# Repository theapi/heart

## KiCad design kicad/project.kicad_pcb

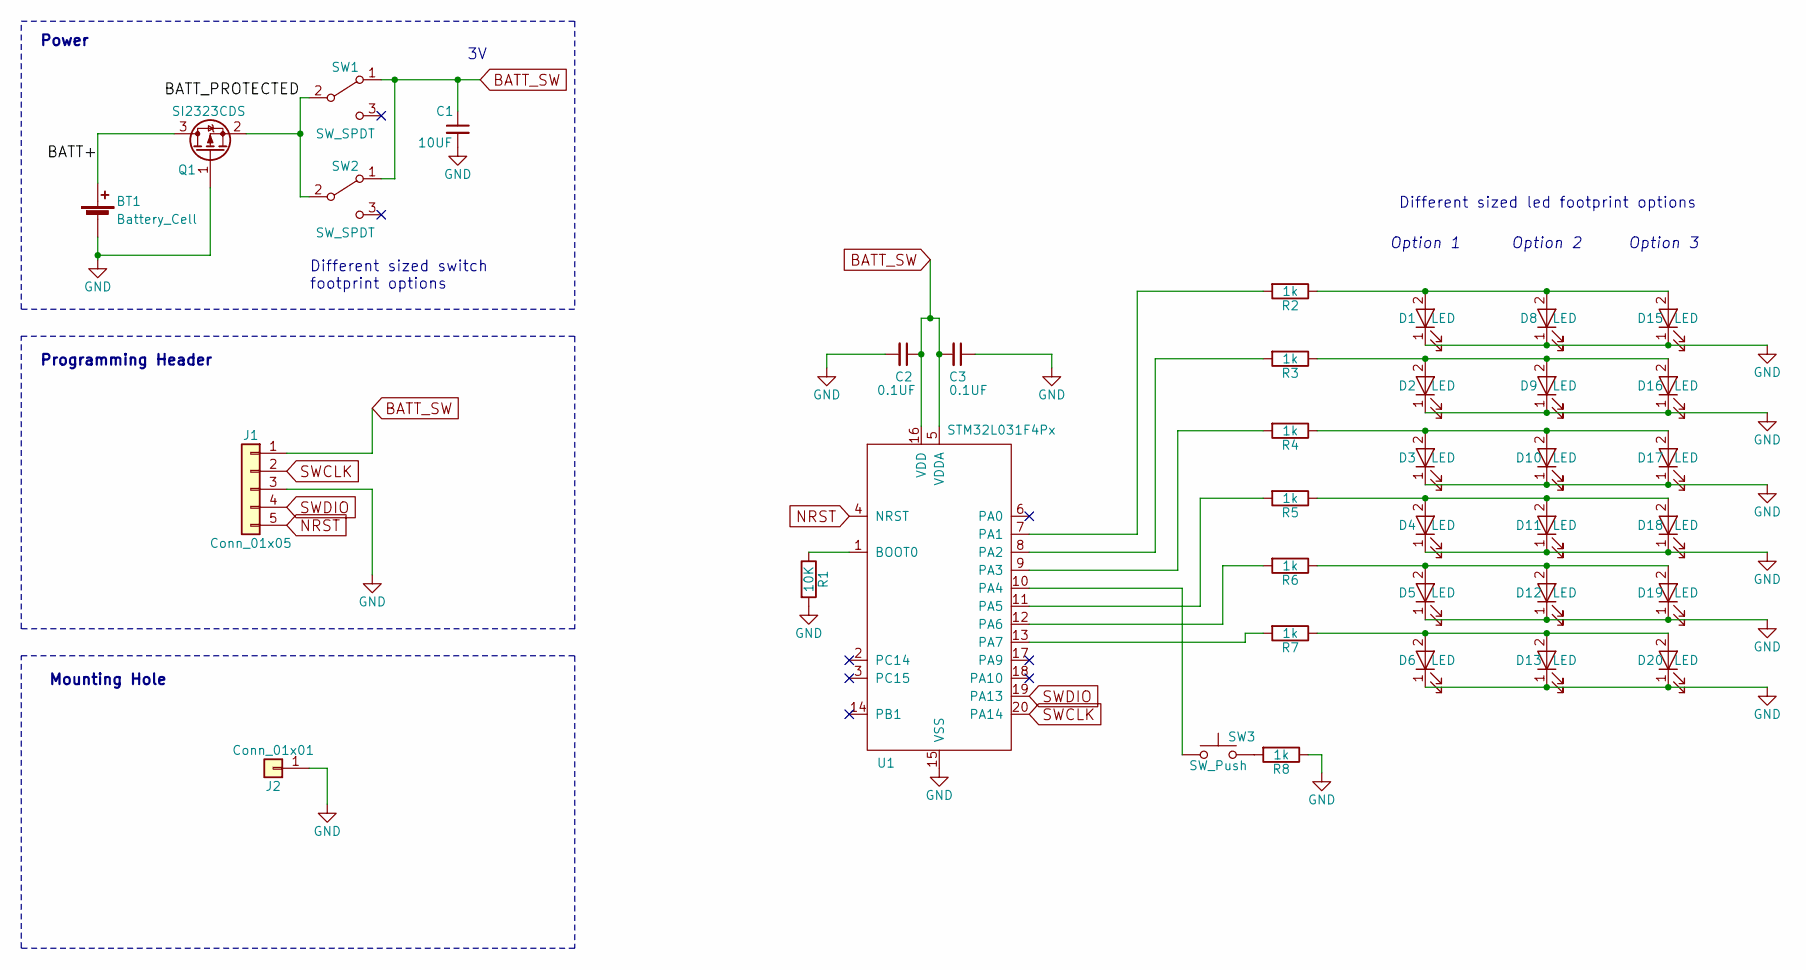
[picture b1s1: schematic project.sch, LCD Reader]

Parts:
BT1: Battery_Cell; CR2032H
C1: 10UF; C_0805_HandSoldering
C2, C3: 0.1UF; C_0805_HandSoldering
D1, D2, D3, D4, D5, D6: LED; LED_0805
D8, D9, D10, D11, D12, D13: LED; LED_D5.0mm
D15, D16, D17, D18, D19, D20: LED; LED_1206
J1: Conn_01x05; SWD_Header
J2: Conn_01x01; MountingHole_2.2mm_M2_ISO7380_Pad
Q1: SI2323CDS; SOT-23_Handsoldering
R1: 10K; R_0603_HandSoldering
R2, R3, R4, R5, R6, R7, R8: 1k; R_0603_HandSoldering
SW1, SW2: SW_SPDT; SW_Micro_SPST
SW3: SW_Push; SW_PUSH_6mm
U1: STM32L031F4Px; TSSOP-20_4.4x6.5mm_Pitch0.65mm

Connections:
/BATT+: BT1.1 (+), Q1.3 (D)
/BATT_PROTECTED: Q1.2 (S), SW1.2 (B), SW2.2 (B)
BATT_SW: C1.1, C2.1, C3.2, J1.1, SW1.1 (A), SW2.1 (A), U1.5 (VDDA), U1.16 (VDD)
GND: BT1.2 (-), C1.2, C2.2, C3.1, D1.1 (K), D2.1 (K), D3.1 (K), D4.1 (K), D5.1 (K), D6.1 (K), D8.1 (K), D9.1 (K), D10.1 (K), D11.1 (K), D12.1 (K), D13.1 (K), D15.1 (K), D16.1 (K), D17.1 (K), D18.1 (K), D19.1 (K), D20.1 (K), J1.3, J2.1, Q1.1 (G), R1.2, R8.1, U1.15 (VSS)
NRST: J1.5, U1.4 (NRST)
unnamed: D1.2 (A), D8.2 (A), D15.2 (A), R2.1
unnamed: D3.2 (A), D10.2 (A), D17.2 (A), R4.1
unnamed: D4.2 (A), D11.2 (A), D18.2 (A), R5.1
unnamed: D5.2 (A), D12.2 (A), D19.2 (A), R6.1
unnamed: D6.2 (A), D13.2 (A), D20.2 (A), R7.1
unnamed: D2.2 (A), D9.2 (A), D16.2 (A), R3.1
unnamed: R1.1, U1.1 (BOOT0)
unnamed: R2.2, U1.7 (PA1)
unnamed: R3.2, U1.8 (PA2)
unnamed: R4.2, U1.9 (PA3)
unnamed: R5.2, U1.11 (PA5)
unnamed: R6.2, U1.12 (PA6)
unnamed: R7.2, U1.13 (PA7)
unnamed: R8.2, SW3.2
unnamed: SW3.1, U1.10 (PA4)
SWCLK: J1.2, U1.20 (PA14)
SWDIO: J1.4, U1.19 (PA13)

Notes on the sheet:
Power
Programming Header
Mounting Hole
Option 1
Option 2
Option 3
Different sized led footprint options
Different sized switch footprint options

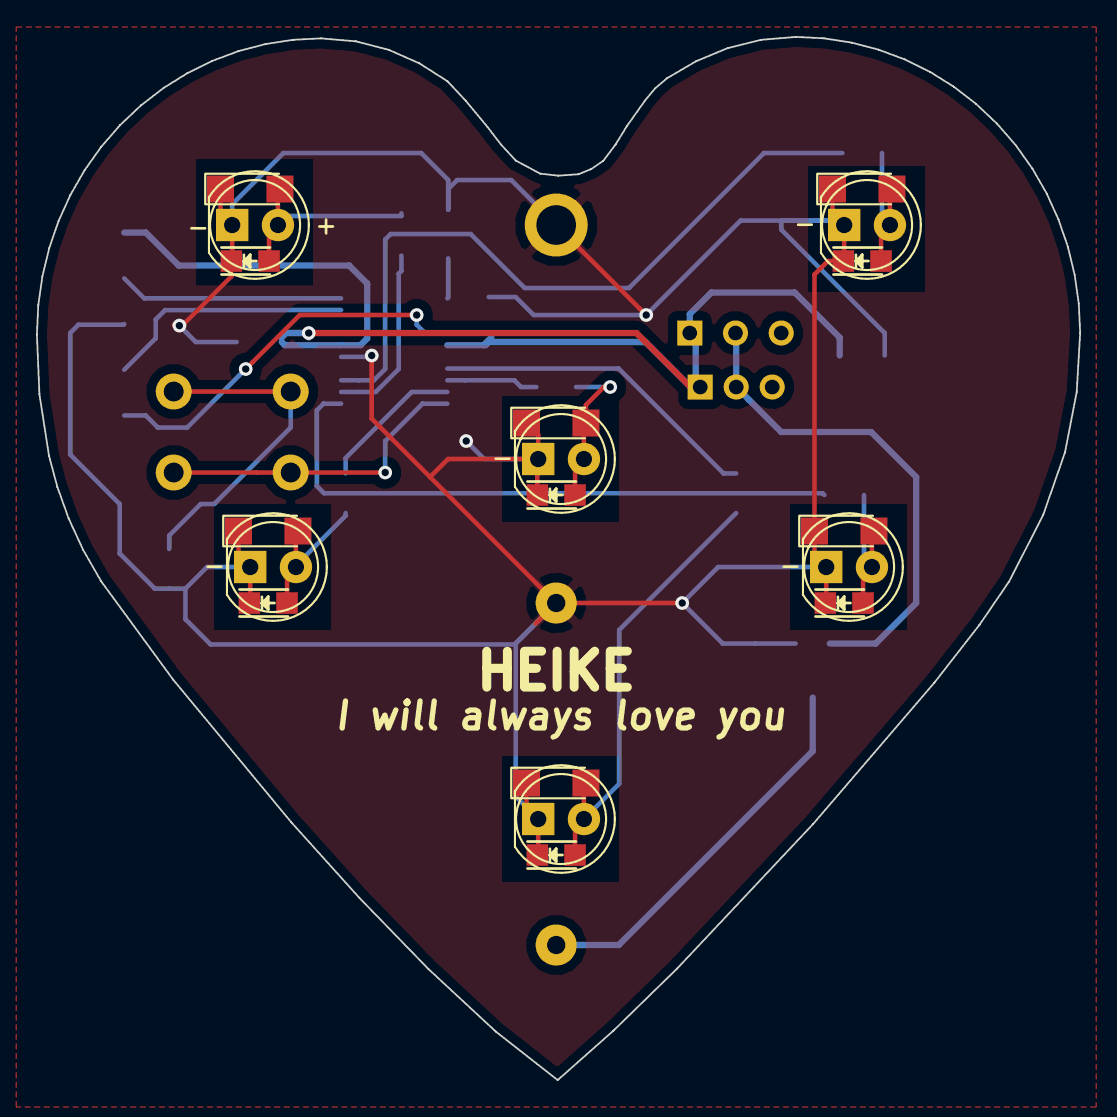
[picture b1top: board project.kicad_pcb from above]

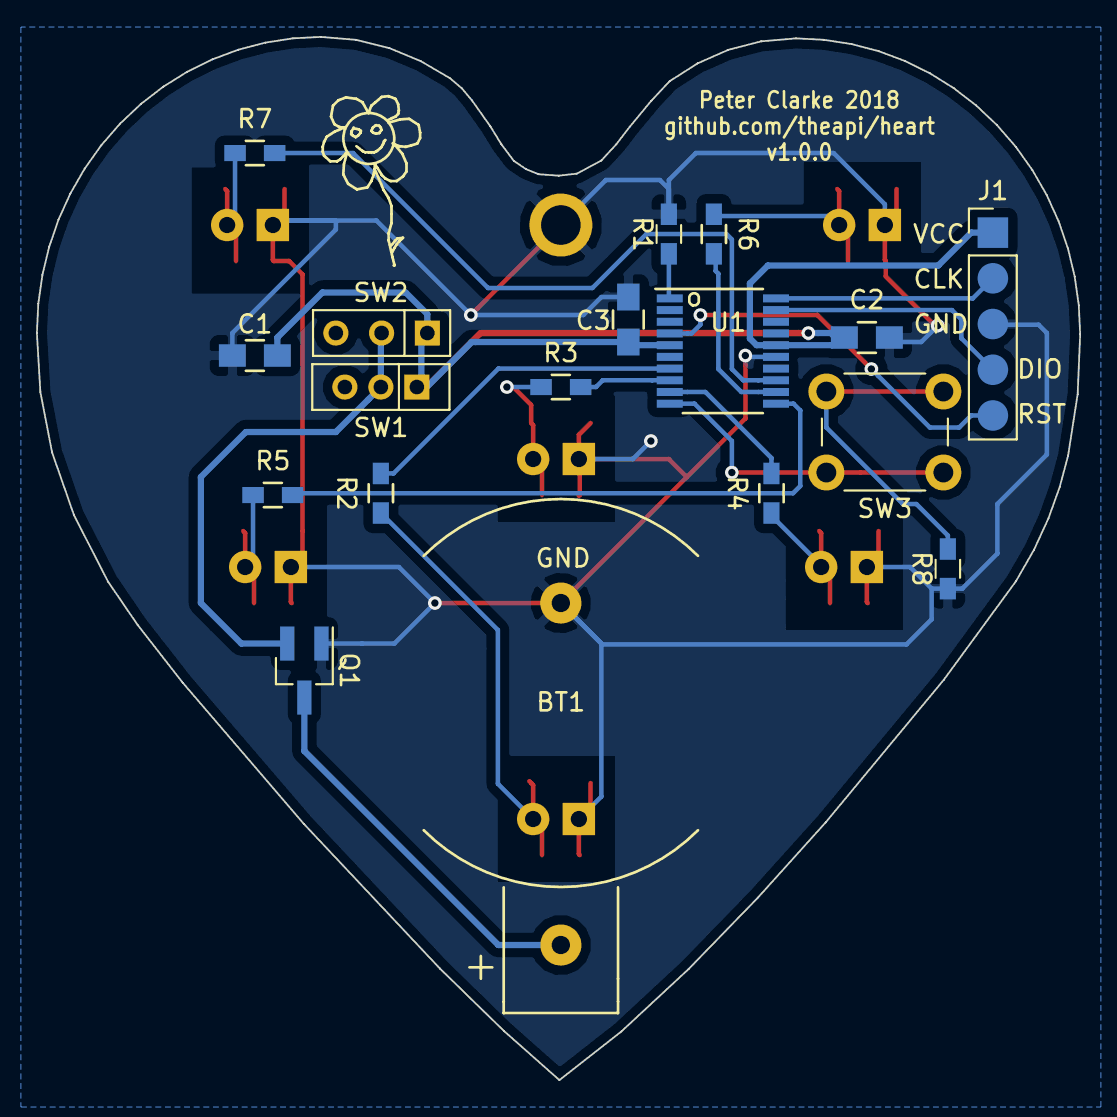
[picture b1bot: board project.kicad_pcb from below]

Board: 2 copper layers, 58.0 x 58.0 mm, 37 parts (18 on the bottom side), 22 nets.

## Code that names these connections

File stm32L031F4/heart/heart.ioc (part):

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Mcu.Name=STM32L031F(4-6)Px
Mcu.Package=TSSOP20
Mcu.UserName=STM32L031F4Px
PA0-CK_IN.Signal=GPIO_Output
PA1.Signal=S_TIM2_CH2
PA13.Mode=Serial_Wire
PA13.Signal=SYS_SWDIO
PA14.Mode=Serial_Wire
PA14.Signal=SYS_SWCLK
PA2.Signal=S_TIM21_CH1
PA3.Signal=S_TIM21_CH2
PA4.GPIOParameters=GPIO_PuPd
PA4.GPIO_PuPd=GPIO_PULLUP
PA4.Signal=GPIO_Input
PA5.Signal=S_TIM2_CH1
PA6.Signal=S_TIM22_CH1
PA7.Signal=S_TIM22_CH2
RCC.HSE_VALUE=8000000
RCC.SYSCLKFreq_VALUE=1048000
board=heart

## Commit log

2018-03-07 Libraries
2018-03-07 Initial config
2018-03-08 Initial led placement
2018-03-08 Fade on the three timers
2018-03-08 7 leds on individual pwm
2018-03-09 Power switch
2018-03-10 19mm between legs of the battery holder
2018-03-10 3 pin push switch
2018-03-10 Heart outline
2018-03-11 Heart board outline
2018-03-12 Allow routing bit to produce the outline
2018-03-17 Better heart outline
2018-03-18 Optional LED footprints
2018-03-18 LEDs layout
2018-03-18 Routing
2018-03-18 Switches
2018-03-20 Reverse polarity protection
2018-03-20 Cap after switch
2018-03-20 Labels
2018-03-20 Copper pour
2018-03-20 Better outline & decorations
2018-03-20 More room for the upright switch
2018-03-20 Gerbers
2018-03-21 Also fit the premade mould from China
2018-03-21 Moved the mosfet away from the battery
2018-03-23 Pin config
2018-03-23 Fade all the leds
2018-03-24 Button down to stop the fade
2018-03-24 Tidy up
2018-03-24 Fade along a sine wave
2018-03-25 PNP polarity protection
2018-04-02 FreeRTOS
2018-04-03 Use an event group for the button status
2018-04-05 Moved pwm init & sine wave variable declaration
2018-04-05 Set event bits for other patterns
2018-04-05 Clear all bits
2018-04-06 7 possible patterns on 3 bits of the group event
2018-04-07 Pattern task manager
2018-04-07 Switch between two patterns
2018-04-07 Pattern 2 when button down
2018-04-07 Current pattern based on the number of button presses
2018-04-08 Use heap_1 memory management
2018-04-08 Use xEventGroupWaitBits so as not to poll the pattern bits
2018-04-08 Removed redundant event bit setting
2018-04-08 Debounce the button
2018-04-08 Static state
2018-04-15 Slower default fade
2018-04-16 Solder mask between pins of the stm32
2018-04-16 Experimental patterns
2018-04-19 enum for the button state machine
2018-04-19 Pattern 2
2018-04-21 Start of remembering pattern
2018-04-21 patternSelect()
2018-04-21 eeprom working
